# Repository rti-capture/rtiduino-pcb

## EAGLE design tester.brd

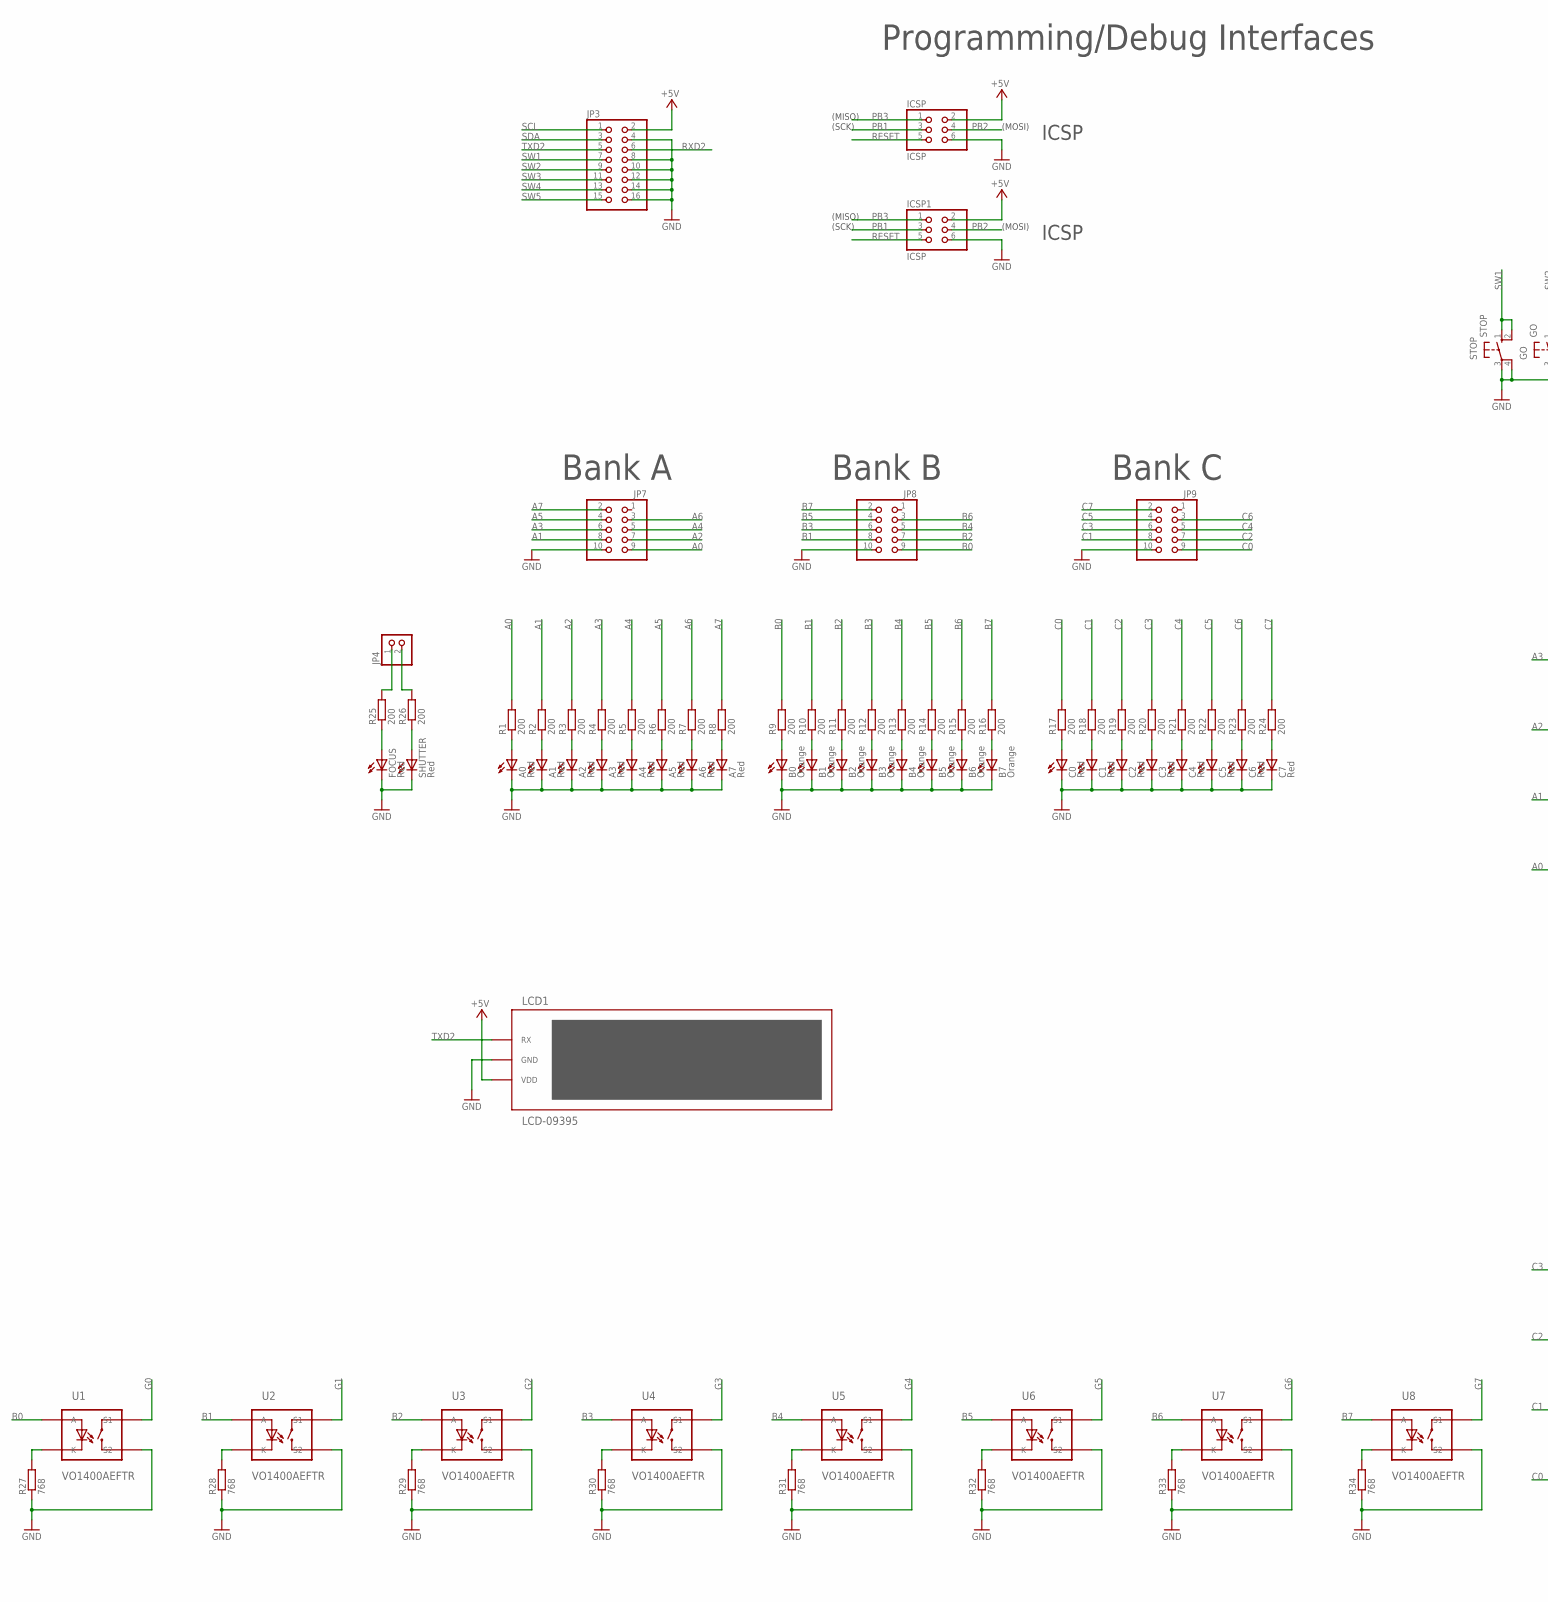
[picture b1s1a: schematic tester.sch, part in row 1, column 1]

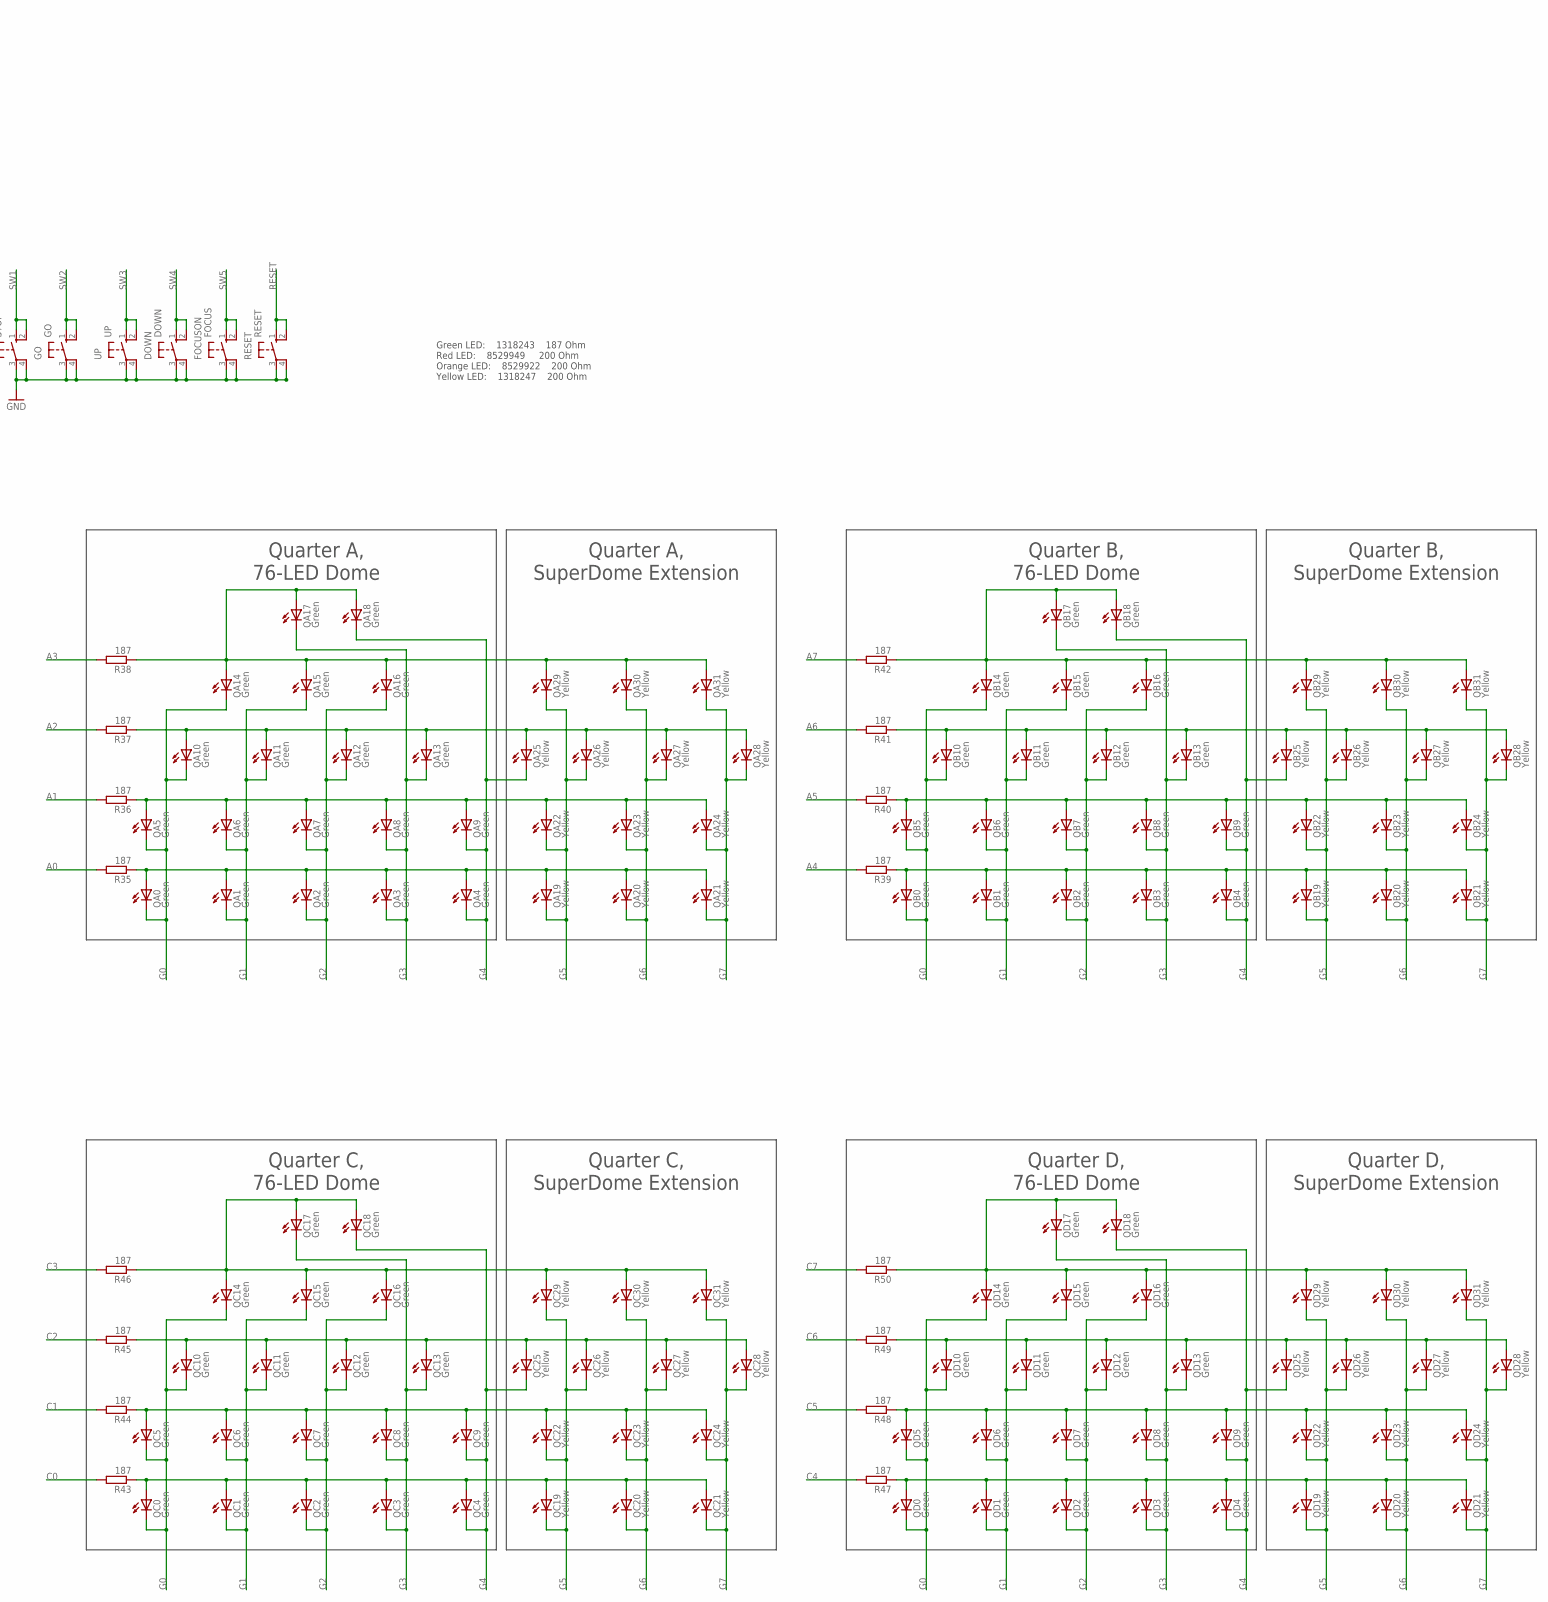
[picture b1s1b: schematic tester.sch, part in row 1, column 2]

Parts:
A0, A1, A2, A3, A4, A5, A6, A7: Red; CHIP-LED0805
B0, B1, B2, B3, B4, B5, B6, B7: Orange; CHIP-LED0805
C0, C1, C2, C3, C4, C5, C6, C7: Red; CHIP-LED0805
DOWN: DOWN; B3F-10XX
FOCUS: Red; CHIP-LED0805
FOCUSON: FOCUS; B3F-10XX
GO: GO; B3F-10XX
ICSP, ICSP1: ICSP; 2X03
JP3: PINHD-2X8; 2X08
JP4: PINHD-1X2; 1X02
JP7, JP8, JP9: PINHD-2X5; 2X05
LCD1: LCD-09395
QA0, QA1, QA2, QA3, QA4, QA5, QA6, QA7, QA8, QA9, QA10, QA11, QA12, QA13, QA14, QA15, QA16, QA17, QA18: Green; CHIP-LED0805
QA19, QA20, QA21, QA22, QA23, QA24, QA25, QA26, QA27, QA28, QA29, QA30, QA31: Yellow; CHIP-LED0805
QB0, QB1, QB2, QB3, QB4, QB5, QB6, QB7, QB8, QB9, QB10, QB11, QB12, QB13, QB14, QB15, QB16, QB17, QB18: Green; CHIP-LED0805
QB19, QB20, QB21, QB22, QB23, QB24, QB25, QB26, QB27, QB28, QB29, QB30, QB31: Yellow; CHIP-LED0805
QC0, QC1, QC2, QC3, QC4, QC5, QC6, QC7, QC8, QC9, QC10, QC11, QC12, QC13, QC14, QC15, QC16, QC17, QC18: Green; CHIP-LED0805
QC19, QC20, QC21, QC22, QC23, QC24, QC25, QC26, QC27, QC28, QC29, QC30, QC31: Yellow; CHIP-LED0805
QD0, QD1, QD2, QD3, QD4, QD5, QD6, QD7, QD8, QD9, QD10, QD11, QD12, QD13, QD14, QD15, QD16, QD17, QD18: Green; CHIP-LED0805
QD19, QD20, QD21, QD22, QD23, QD24, QD25, QD26, QD27, QD28, QD29, QD30, QD31: Yellow; CHIP-LED0805
R1, R2, R3, R4, R5, R6, R7, R8, R9, R10, R11, R12, R13, R14, R15, R16, R17, R18, R19, R20, R21, R22, R23, R24, R25, R26: 200; R0805
R27, R28, R29, R30, R31, R32, R33, R34: 768; R0805
R35, R36, R37, R38, R39, R40, R41, R42, R43, R44, R45, R46, R47, R48, R49, R50: 187; R0805
RESET: RESET; B3F-10XX
SHUTTER: Red; CHIP-LED0805
STOP: STOP; B3F-10XX
U1, U2, U3, U4, U5, U6, U7, U8: VO1400AEFTR; SOP4
UP: UP; B3F-10XX

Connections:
+5V: ICSP.2, ICSP1.2, JP3.2, LCD1.P$3 (VDD)
A0: JP7.9, R1.2, R35.2
A1: JP7.8, R2.2, R36.2
A2: JP7.7, R3.2, R37.2
A3: JP7.6, R4.2, R38.2
A4: JP7.5, R5.2, R39.2
A5: JP7.4, R6.2, R40.2
A6: JP7.3, R7.2, R41.2
A7: JP7.2, R8.2, R42.2
B0: JP8.9, R9.2, U1.P$1 (A)
B1: JP8.8, R10.2, U2.P$1 (A)
B2: JP8.7, R11.2, U3.P$1 (A)
B3: JP8.6, R12.2, U4.P$1 (A)
B4: JP8.5, R13.2, U5.P$1 (A)
B5: JP8.4, R14.2, U6.P$1 (A)
B6: JP8.3, R15.2, U7.P$1 (A)
B7: JP8.2, R16.2, U8.P$1 (A)
C0: JP9.9, R17.2, R43.2
C1: JP9.8, R18.2, R44.2
C2: JP9.7, R19.2, R45.2
C3: JP9.6, R20.2, R46.2
C4: JP9.5, R21.2, R47.2
C5: JP9.4, R22.2, R48.2
C6: JP9.3, R23.2, R49.2
C7: JP9.2, R24.2, R50.2
FOCUS: JP4.1, R25.2
G0: QA0.C, QA5.C, QA10.C, QA14.C, QB0.C, QB5.C, QB10.C, QB14.C, QC0.C, QC5.C, QC10.C, QC14.C, QD0.C, QD5.C, QD10.C, QD14.C, U1.P$4 (S1)
G1: QA1.C, QA6.C, QA11.C, QA15.C, QB1.C, QB6.C, QB11.C, QB15.C, QC1.C, QC6.C, QC11.C, QC15.C, QD1.C, QD6.C, QD11.C, QD15.C, U2.P$4 (S1)
G2: QA2.C, QA7.C, QA12.C, QA16.C, QB2.C, QB7.C, QB12.C, QB16.C, QC2.C, QC7.C, QC12.C, QC16.C, QD2.C, QD7.C, QD12.C, QD16.C, U3.P$4 (S1)
G3: QA3.C, QA8.C, QA13.C, QA17.C, QB3.C, QB8.C, QB13.C, QB17.C, QC3.C, QC8.C, QC13.C, QC17.C, QD3.C, QD8.C, QD13.C, QD17.C, U4.P$4 (S1)
G4: QA4.C, QA9.C, QA18.C, QA25.C, QB4.C, QB9.C, QB18.C, QB25.C, QC4.C, QC9.C, QC18.C, QC25.C, QD4.C, QD9.C, QD18.C, QD25.C, U5.P$4 (S1)
G5: QA19.C, QA22.C, QA26.C, QA29.C, QB19.C, QB22.C, QB26.C, QB29.C, QC19.C, QC22.C, QC26.C, QC29.C, QD19.C, QD22.C, QD26.C, QD29.C, U6.P$4 (S1)
G6: QA20.C, QA23.C, QA27.C, QA30.C, QB20.C, QB23.C, QB27.C, QB30.C, QC20.C, QC23.C, QC27.C, QC30.C, QD20.C, QD23.C, QD27.C, QD30.C, U7.P$4 (S1)
G7: QA21.C, QA24.C, QA28.C, QA31.C, QB21.C, QB24.C, QB28.C, QB31.C, QC21.C, QC24.C, QC28.C, QC31.C, QD21.C, QD24.C, QD28.C, QD31.C, U8.P$4 (S1)
GND: A0.C, A1.C, A2.C, A3.C, A4.C, A5.C, A6.C, A7.C, B0.C, B1.C, B2.C, B3.C, B4.C, B5.C, B6.C, B7.C, C0.C, C1.C, C2.C, C3.C, C4.C, C5.C, C6.C, C7.C, DOWN.3, DOWN.4 (P1), FOCUS.C, FOCUSON.3, FOCUSON.4 (P1), GO.3, GO.4 (P1), ICSP.6, ICSP1.6, JP3.4, JP3.8, JP3.10, JP3.12, JP3.14, JP3.16, JP7.10, JP8.10, JP9.10, LCD1.P$2 (GND), R27.1, R28.1, R29.1, R30.1, R31.1, R32.1, R33.1, R34.1, RESET.3, RESET.4 (P1), SHUTTER.C, STOP.3, STOP.4 (P1), U1.P$3 (S2), U2.P$3 (S2), U3.P$3 (S2), U4.P$3 (S2), U5.P$3 (S2), U6.P$3 (S2), U7.P$3 (S2), U8.P$3 (S2), UP.3, UP.4 (P1)
unnamed: A0.A, R1.1
unnamed: A1.A, R2.1
unnamed: A2.A, R3.1
unnamed: A3.A, R4.1
unnamed: A4.A, R5.1
unnamed: A5.A, R6.1
unnamed: A6.A, R7.1
unnamed: A7.A, R8.1
unnamed: FOCUS.A, R25.1
unnamed: B0.A, R9.1
unnamed: B1.A, R10.1
unnamed: B2.A, R11.1
unnamed: B3.A, R12.1
unnamed: B4.A, R13.1
unnamed: B5.A, R14.1
unnamed: B6.A, R15.1
unnamed: B7.A, R16.1
unnamed: C0.A, R17.1
unnamed: C1.A, R18.1
unnamed: C2.A, R19.1
unnamed: C3.A, R20.1
unnamed: C4.A, R21.1
unnamed: C5.A, R22.1
unnamed: C6.A, R23.1
unnamed: C7.A, R24.1
unnamed: R26.1, SHUTTER.A
unnamed: R27.2, U1.P$2 (K)
unnamed: R28.2, U2.P$2 (K)
unnamed: QA0.A, QA1.A, QA2.A, QA3.A, QA4.A, QA19.A, QA20.A, QA21.A, R35.1
unnamed: QA5.A, QA6.A, QA7.A, QA8.A, QA9.A, QA22.A, QA23.A, QA24.A, R36.1
unnamed: QA10.A, QA11.A, QA12.A, QA13.A, QA25.A, QA26.A, QA27.A, QA28.A, R37.1
unnamed: QA14.A, QA15.A, QA16.A, QA17.A, QA18.A, QA29.A, QA30.A, QA31.A, R38.1
unnamed: R29.2, U3.P$2 (K)
unnamed: QB0.A, QB1.A, QB2.A, QB3.A, QB4.A, QB19.A, QB20.A, QB21.A, R39.1
unnamed: QB5.A, QB6.A, QB7.A, QB8.A, QB9.A, QB22.A, QB23.A, QB24.A, R40.1
unnamed: QB10.A, QB11.A, QB12.A, QB13.A, QB25.A, QB26.A, QB27.A, QB28.A, R41.1
unnamed: QB14.A, QB15.A, QB16.A, QB17.A, QB18.A, QB29.A, QB30.A, QB31.A, R42.1
unnamed: QC0.A, QC1.A, QC2.A, QC3.A, QC4.A, QC19.A, QC20.A, QC21.A, R43.1
unnamed: QC5.A, QC6.A, QC7.A, QC8.A, QC9.A, QC22.A, QC23.A, QC24.A, R44.1
unnamed: QC10.A, QC11.A, QC12.A, QC13.A, QC25.A, QC26.A, QC27.A, QC28.A, R45.1
unnamed: QC14.A, QC15.A, QC16.A, QC17.A, QC18.A, QC29.A, QC30.A, QC31.A, R46.1
unnamed: QD0.A, QD1.A, QD2.A, QD3.A, QD4.A, QD19.A, QD20.A, QD21.A, R47.1
unnamed: QD5.A, QD6.A, QD7.A, QD8.A, QD9.A, QD22.A, QD23.A, QD24.A, R48.1
unnamed: QD10.A, QD11.A, QD12.A, QD13.A, QD25.A, QD26.A, QD27.A, QD28.A, R49.1
unnamed: QD14.A, QD15.A, QD16.A, QD17.A, QD18.A, QD29.A, QD30.A, QD31.A, R50.1
unnamed: R30.2, U4.P$2 (K)
unnamed: R31.2, U5.P$2 (K)
unnamed: R32.2, U6.P$2 (K)
unnamed: R33.2, U7.P$2 (K)
unnamed: R34.2, U8.P$2 (K)
PB1: ICSP.3, ICSP1.3
PB2: ICSP.4, ICSP1.4
PB3: ICSP.1, ICSP1.1
RESET: ICSP.5, ICSP1.5, RESET.1 (S), RESET.2 (S1)
RXD2: JP3.6
SCL: JP3.1
SDA: JP3.3
SHUTTER: JP4.2, R26.2
SW1: JP3.7, STOP.1 (S), STOP.2 (S1)
SW2: GO.1 (S), GO.2 (S1), JP3.9
SW3: JP3.11, UP.1 (S), UP.2 (S1)
SW4: DOWN.1 (S), DOWN.2 (S1), JP3.13
SW5: FOCUSON.1 (S), FOCUSON.2 (S1), JP3.15
TXD2: JP3.5, LCD1.P$1 (RX)

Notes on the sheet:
(SCK)
(MISO)
(MOSI)
Programming/Debug Interfaces
ICSP
Bank A
Bank B
Bank C
Quarter A, 76-LED Dome
Quarter A, SuperDome Extension
Quarter B, 76-LED Dome
Quarter B, SuperDome Extension
Quarter C, 76-LED Dome
Quarter C, SuperDome Extension
Quarter D, 76-LED Dome
Quarter D, SuperDome Extension
Green LED: 1318243 187 Ohm Red LED: 8529949 200 Ohm Orange LED: 8529922 200 Ohm Yellow LED: 1318247 200 Ohm

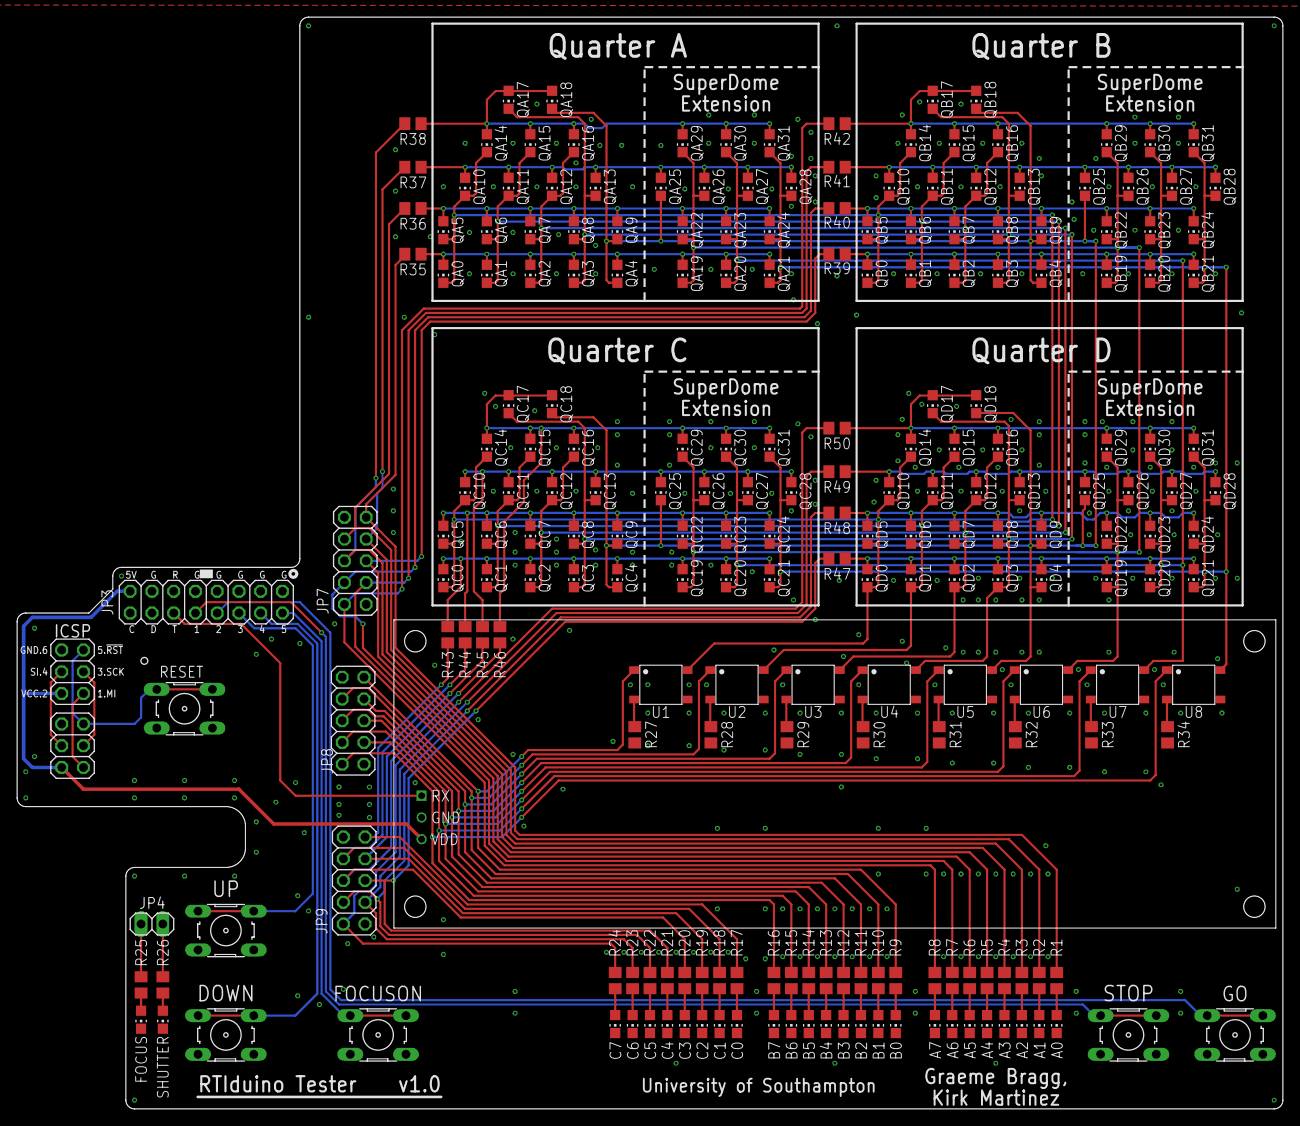
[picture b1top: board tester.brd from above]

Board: 2 copper layers, 147.8 x 127.5 mm, 226 parts (0 on the bottom side), 96 nets.

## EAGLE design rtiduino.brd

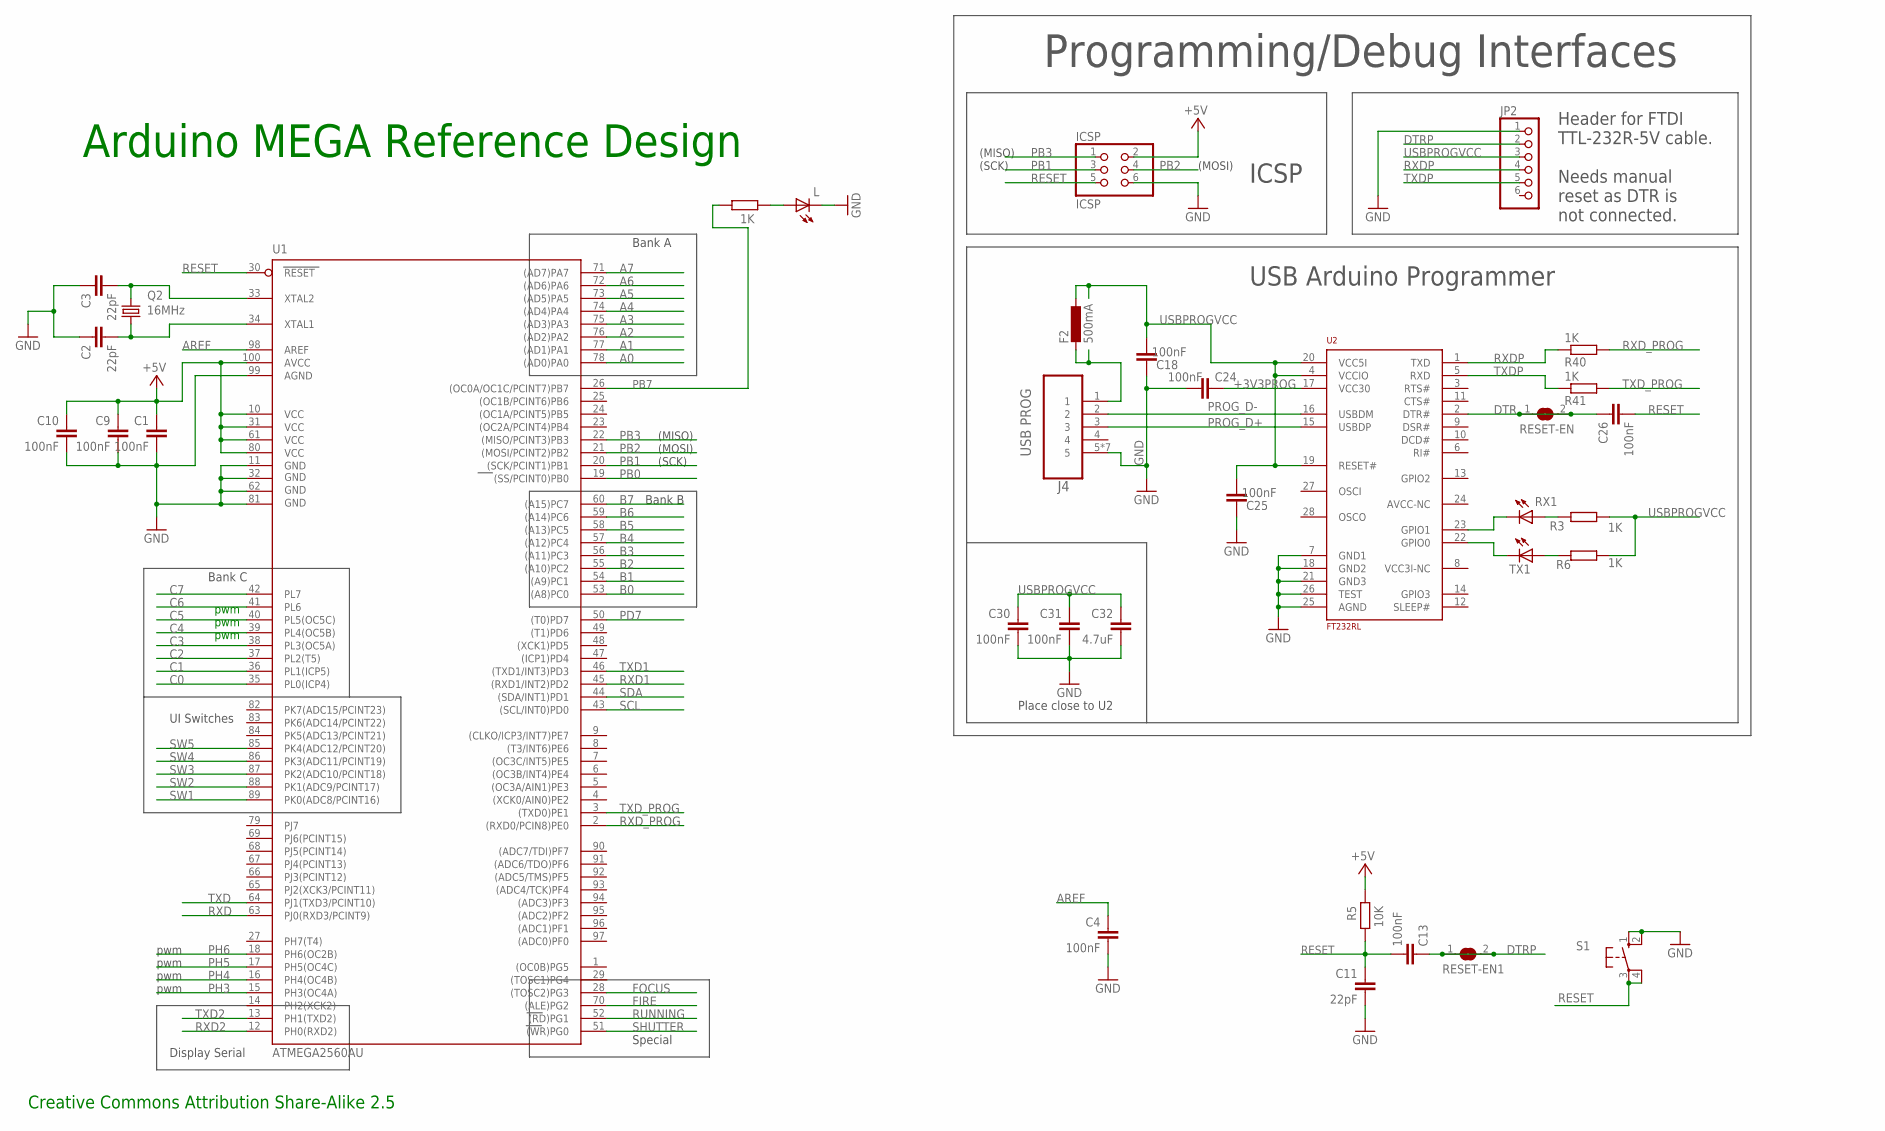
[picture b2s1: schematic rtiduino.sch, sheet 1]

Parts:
C1, C4, C9, C10, C13, C18, C24, C25, C26, C30, C31: 100nF; C0805K
C2, C3, C11: 22pF; C0805K
C32: 4.7uF; C0805K
F2: 500mA; L1812
ICSP: ICSP; 2X03
J4: USB PROG; MOLEX_47346-0001
JP2: PINHD-1X6; 1X06
L: LEDCHIP-LED0805; CHIP-LED0805
Q2: 16MHz; HC49/S
R1, R3, R6, R40, R41: 1K; R0805
R5: 10K; R0805
RESET-EN, RESET-EN1: SJ
RX1: LEDCHIP-LED0805; CHIP-LED0805
S1: 10-XX; B3F-10XX
TX1: LEDCHIP-LED0805; CHIP-LED0805
U1: ATMEGA2560AU; TQFP100
U2: FT232RL; SSOP28

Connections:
+3V3PROG: C24.2, U2.17 (VCC30)
+5V: C1.1, C9.1, C10.1, ICSP.2, R5.2, U1.10 (VCC), U1.31 (VCC1), U1.61 (VCC2), U1.80 (VCC3), U1.100 (AVCC); also elsewhere on the board
A0: U1.78 ((AD0)PA0); also elsewhere on the board
A1: U1.77 ((AD1)PA1); also elsewhere on the board
A2: U1.76 ((AD2)PA2); also elsewhere on the board
A3: U1.75 ((AD3)PA3); also elsewhere on the board
A4: U1.74 ((AD4)PA4); also elsewhere on the board
A5: U1.73 ((AD5)PA5); also elsewhere on the board
A6: U1.72 ((AD6)PA6); also elsewhere on the board
A7: U1.71 ((AD7)PA7); also elsewhere on the board
AREF: C4.1, U1.98 (AREF)
B0: U1.53 ((A8)PC0); also elsewhere on the board
B1: U1.54 ((A9)PC1); also elsewhere on the board
B2: U1.55 ((A10)PC2); also elsewhere on the board
B3: U1.56 ((A11)PC3); also elsewhere on the board
B4: U1.57 ((A12)PC4); also elsewhere on the board
B5: U1.58 ((A13)PC5); also elsewhere on the board
B6: U1.59 ((A14)PC6); also elsewhere on the board
B7: U1.60 ((A15)PC7); also elsewhere on the board
C0: U1.35 (PL0(ICP4)); also elsewhere on the board
C1: U1.36 (PL1(ICP5)); also elsewhere on the board
C2: U1.37 (PL2(T5)); also elsewhere on the board
C3: U1.38 (PL3(OC5A)); also elsewhere on the board
C4: U1.39 (PL4(OC5B)); also elsewhere on the board
C5: U1.40 (PL5(OC5C)); also elsewhere on the board
C6: U1.41 (PL6); also elsewhere on the board
C7: U1.42 (PL7); also elsewhere on the board
DTR: C26.1, RESET-EN.1, RESET-EN.2, U2.2 (DTR#)
DTRP: C13.1, JP2.2, RESET-EN1.1, RESET-EN1.2
FIRE: U1.70 ((ALE)PG2); also elsewhere on the board
FOCUS: U1.28 ((TOSC2)PG3); also elsewhere on the board
GND: C1.2, C2.1, C3.1, C4.2, C9.2, C10.2, C11.2, C18.2, C24.1, C25.2, C30.2, C31.2, C32.2, ICSP.6, J4.5, J4.M1 (5), J4.M2 (5), J4.M3 (5), J4.M4 (5), J4.M5 (5), J4.M6 (5), JP2.1, L.C, S1.1 (S), S1.2 (S1), U1.11 (GND), U1.32 (GND1), U1.62 (GND2), U1.81 (GND3), U1.99 (AGND), U2.7 (GND1), U2.18 (GND2), U2.21 (GND3), U2.25 (AGND), U2.26 (TEST); also elsewhere on the board
unnamed: L.A, R1.2
unnamed: C2.2, Q2.1, U1.34 (XTAL1)
unnamed: C3.2, Q2.2, U1.33 (XTAL2)
unnamed: RX1.C, U2.23 (GPIO1)
unnamed: TX1.C, U2.22 (GPIO0)
unnamed: R3.1, RX1.A
unnamed: R6.1, TX1.A
unnamed: F2.2, J4.1
PB0: U1.19 ((SS/PCINT0)PB0)
PB1: ICSP.3, U1.20 ((SCK/PCINT1)PB1)
PB2: ICSP.4, U1.21 ((MOSI/PCINT2)PB2)
PB3: ICSP.1, U1.22 ((MISO/PCINT3)PB3)
PB7: R1.1, U1.26 ((OC0A/OC1C/PCINT7)PB7)
PD7: U1.50 ((T0)PD7)
PH3: U1.15 (PH3(OC4A))
PH4: U1.16 (PH4(OC4B))
PH5: U1.17 (PH5(OC4C))
PH6: U1.18 (PH6(OC2B))
PROG_D+: J4.3, U2.15 (USBDP)
PROG_D-: J4.2, U2.16 (USBDM)
RESET: C11.1, C13.2, C26.2, ICSP.5, R5.1, S1.3, S1.4 (P1), U1.30 (RESET)
RUNNING: U1.52 ((RD)PG1); also elsewhere on the board
RXD: U1.63 (PJ0(RXD3/PCINT9)); also elsewhere on the board
RXD1: U1.45 ((RXD1/INT2)PD2)
RXD2: U1.12 (PH0(RXD2)); also elsewhere on the board
RXDP: JP2.4, R40.1, U2.1 (TXD)
RXD_PROG: R40.2, U1.2 ((RXD0/PCIN8)PE0)
SCL: U1.43 ((SCL/INT0)PD0); also elsewhere on the board
SDA: U1.44 ((SDA/INT1)PD1); also elsewhere on the board
SHUTTER: U1.51 ((WR)PG0); also elsewhere on the board
SW1: U1.89 (PK0(ADC8/PCINT16)); also elsewhere on the board
SW2: U1.88 (PK1(ADC9/PCINT17)); also elsewhere on the board
SW3: U1.87 (PK2(ADC10/PCINT18)); also elsewhere on the board
SW4: U1.86 (PK3(ADC11/PCINT19)); also elsewhere on the board
SW5: U1.85 (PK4(ADC12/PCINT20)); also elsewhere on the board
TXD: U1.64 (PJ1(TXD3/PCINT10)); also elsewhere on the board
TXD1: U1.46 ((TXD1/INT3)PD3)
TXD2: U1.13 (PH1(TXD2)); also elsewhere on the board
TXDP: JP2.5, R41.1, U2.5 (RXD)
TXD_PROG: R41.2, U1.3 ((TXD0)PE1)
USBPROGVCC: C18.1, C25.1, C30.1, C31.1, C32.1, F2.1, JP2.3, R3.2, R6.2, U2.4 (VCCIO), U2.19 (RESET#), U2.20 (VCC5I); also elsewhere on the board

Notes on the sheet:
Arduino MEGA Reference Design
(SCK)
(MISO)
(MOSI)
pwm
Creative Commons Attribution Share-Alike 2.5
Bank A
Bank B
Bank C
Special
Place close to U2
Programming/Debug Interfaces
ICSP
USB Arduino Programmer
Header for FTDI TTL-232R-5V cable. Needs manual reset as DTR is not connected.
UI Switches
Display Serial

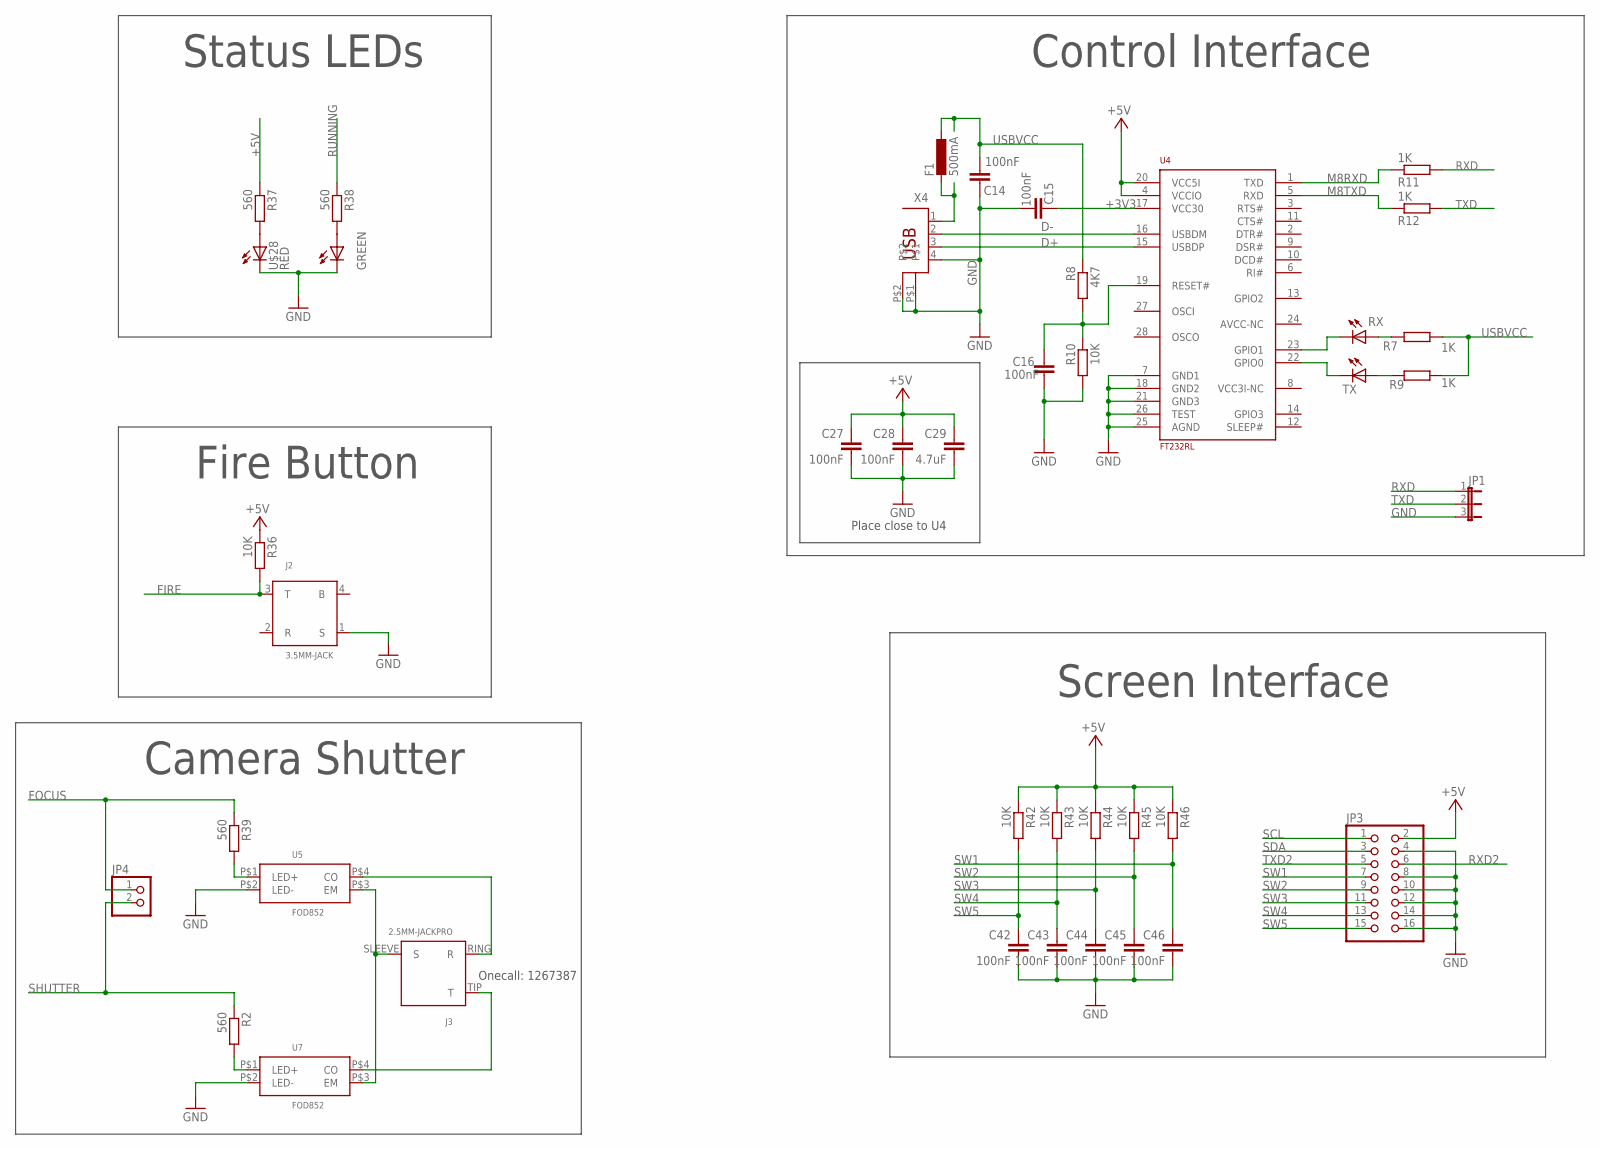
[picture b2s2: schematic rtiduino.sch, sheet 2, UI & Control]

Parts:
C14, C15, C16, C27, C28, C42, C43, C44, C45, C46: 100nF; C0805K
C29: 4.7uF; C0805K
F1: 500mA; L1812
J2: 3.5MM-JACK; 3.5-JACK-RA
J3: 2.5MM-JACKPRO; 2.5-JACK-RA-PRO
JP1: JP2E; JP2
JP3: PINHD-2X8; 2X08
JP4: PINHD-1X2; 1X02
R2, R37, R38, R39: 560; R0805
R7, R9, R11, R12: 1K; R0805
R8: 4K7; R0805
R10, R36, R42, R43, R44, R45, R46: 10K; R0805
RX: LEDCHIP-LED0805; CHIP-LED0805
TX: LEDCHIP-LED0805; CHIP-LED0805
U4: FT232RL; SSOP28
U5, U7: FOD852; DIP4-SMD
U$28: 122-000-04-52
X4: PN61729

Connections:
+3V3: C15.2, U4.17 (VCC30)
+5V: C27.1, C28.1, C29.1, JP3.2, R36.1, R37.1, R42.1, R43.1, R44.1, R45.1, R46.1, U4.4 (VCCIO), U4.20 (VCC5I); also elsewhere on the board
CAM_GND: J3.SLEEVE (S), U5.P$3 (EM), U7.P$3 (EM)
CAM_RING: J3.RING (R), U5.P$4 (CO)
CAM_SHUTTER: J3.TIP (T), U7.P$4 (CO)
D+: U4.15 (USBDP), X4.3
D-: U4.16 (USBDM), X4.2
FIRE: J2.3 (T), R36.2; also elsewhere on the board
FOCUS: JP4.1, R39.1; also elsewhere on the board
GND: C14.2, C15.1, C16.1, C27.2, C28.2, C29.2, C42.2, C43.2, C44.2, C45.2, C46.2, J2.1 (S), JP1.3, JP3.4, JP3.8, JP3.10, JP3.12, JP3.14, JP3.16, R10.2, U4.7 (GND1), U4.18 (GND2), U4.21 (GND3), U4.25 (AGND), U4.26 (TEST), U5.P$2 (LED-), U7.P$2 (LED-), U$28.P$1 (RC), U$28.P$3 (GC), X4.4, X4.P$1, X4.P$2; also elsewhere on the board
M8RXD: R11.1, U4.1 (TXD)
M8TXD: R12.1, U4.5 (RXD)
unnamed: RX.C, U4.23 (GPIO1)
unnamed: TX.C, U4.22 (GPIO0)
unnamed: R7.1, RX.A
unnamed: R9.1, TX.A
unnamed: R37.2, U$28.P$2 (RA)
unnamed: R38.2, U$28.P$4 (GA)
unnamed: R39.2, U5.P$1 (LED+)
unnamed: F1.2, X4.1
unnamed: R2.2, U7.P$1 (LED+)
unnamed: C16.2, R8.2, R10.1, U4.19 (RESET#)
RUNNING: R38.1; also elsewhere on the board
RXD: JP1.1, R11.2; also elsewhere on the board
RXD2: JP3.6; also elsewhere on the board
SCL: JP3.1; also elsewhere on the board
SDA: JP3.3; also elsewhere on the board
SHUTTER: JP4.2, R2.1; also elsewhere on the board
SW1: C46.1, JP3.7, R46.2; also elsewhere on the board
SW2: C45.1, JP3.9, R45.2; also elsewhere on the board
SW3: C44.1, JP3.11, R44.2; also elsewhere on the board
SW4: C43.1, JP3.13, R43.2; also elsewhere on the board
SW5: C42.1, JP3.15, R42.2; also elsewhere on the board
TXD: JP1.2, R12.2; also elsewhere on the board
TXD2: JP3.5; also elsewhere on the board
USBVCC: C14.1, F1.1, R7.2, R8.1, R9.2; also elsewhere on the board

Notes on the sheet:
Place close to U4
Control Interface
Status LEDs
Fire Button
Camera Shutter
Screen Interface
Onecall: 1267387

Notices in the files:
parts and their libraries:
SparkFun: Licensing: CC v3.0 Share-Alike You are welcome to use this library for commercial purposes.
